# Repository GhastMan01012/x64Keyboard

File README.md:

# x64Keyboard
Source for x64 design

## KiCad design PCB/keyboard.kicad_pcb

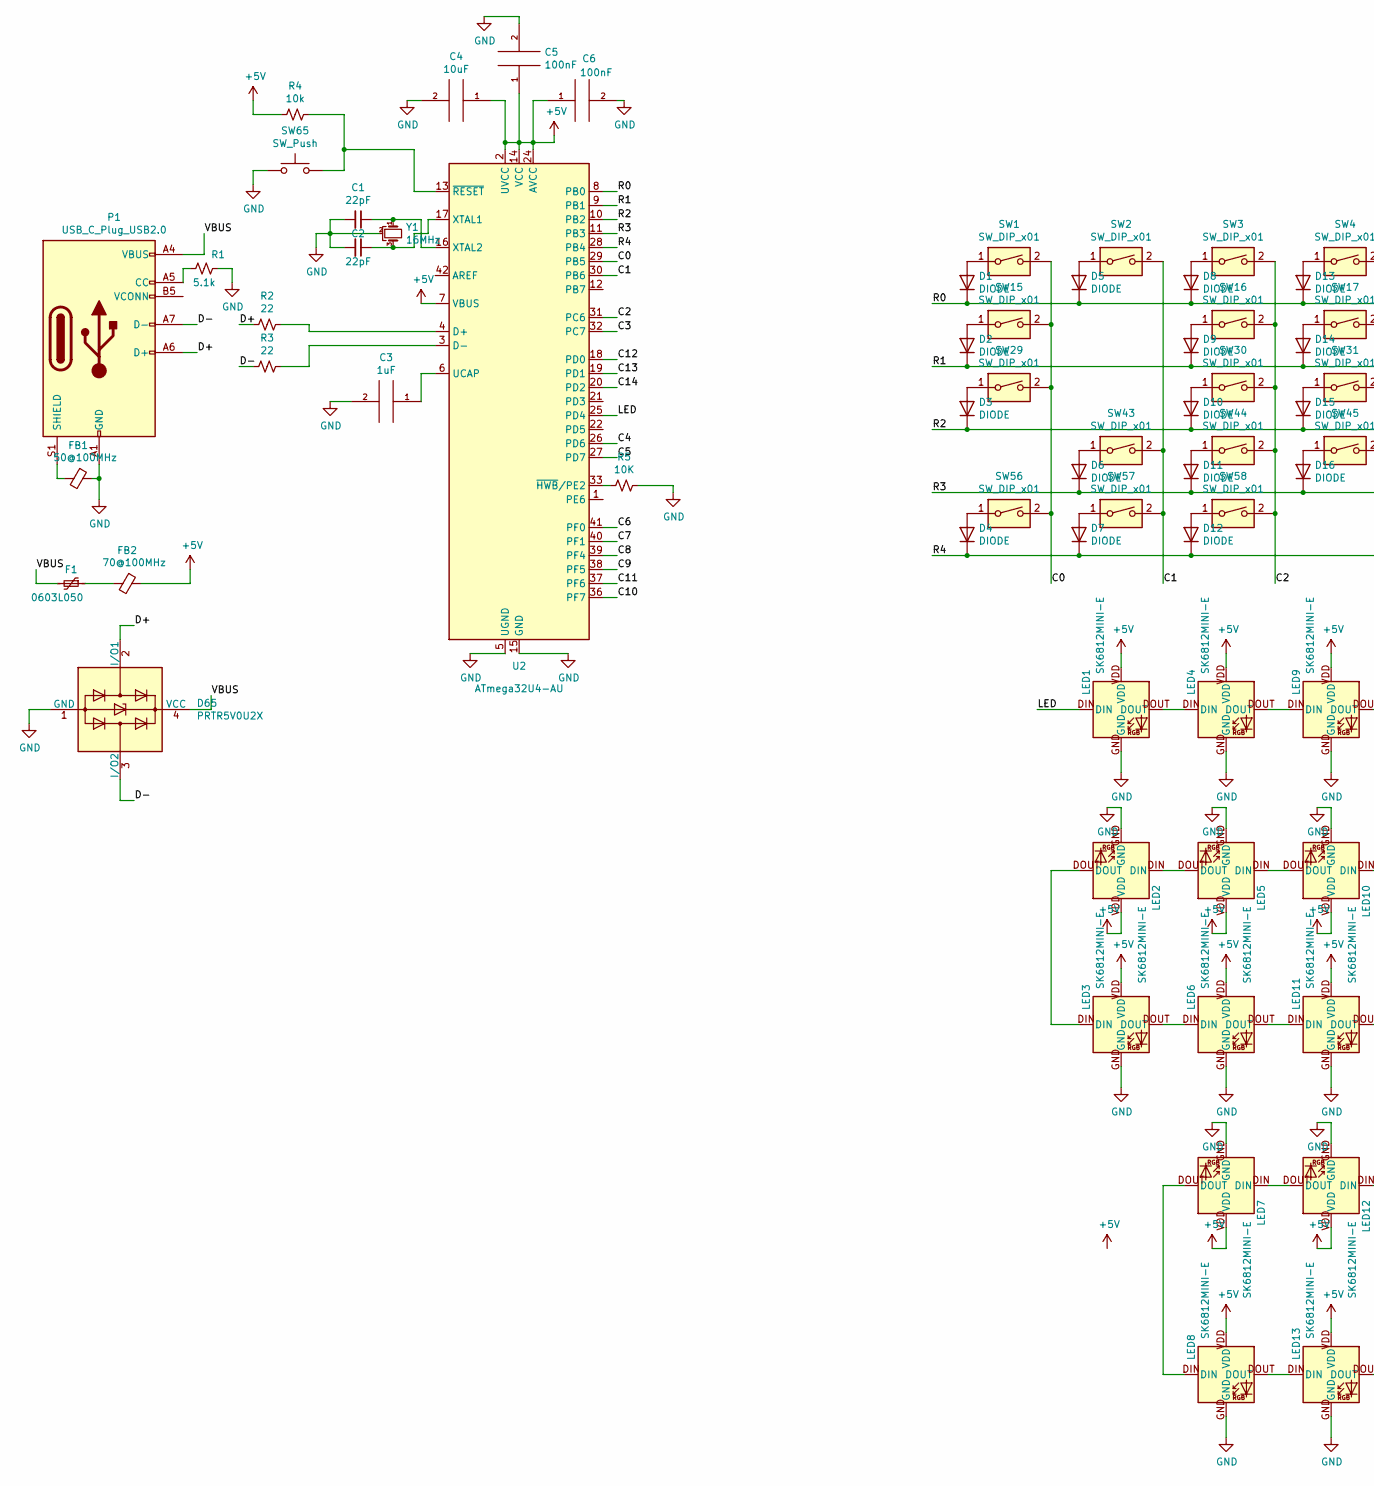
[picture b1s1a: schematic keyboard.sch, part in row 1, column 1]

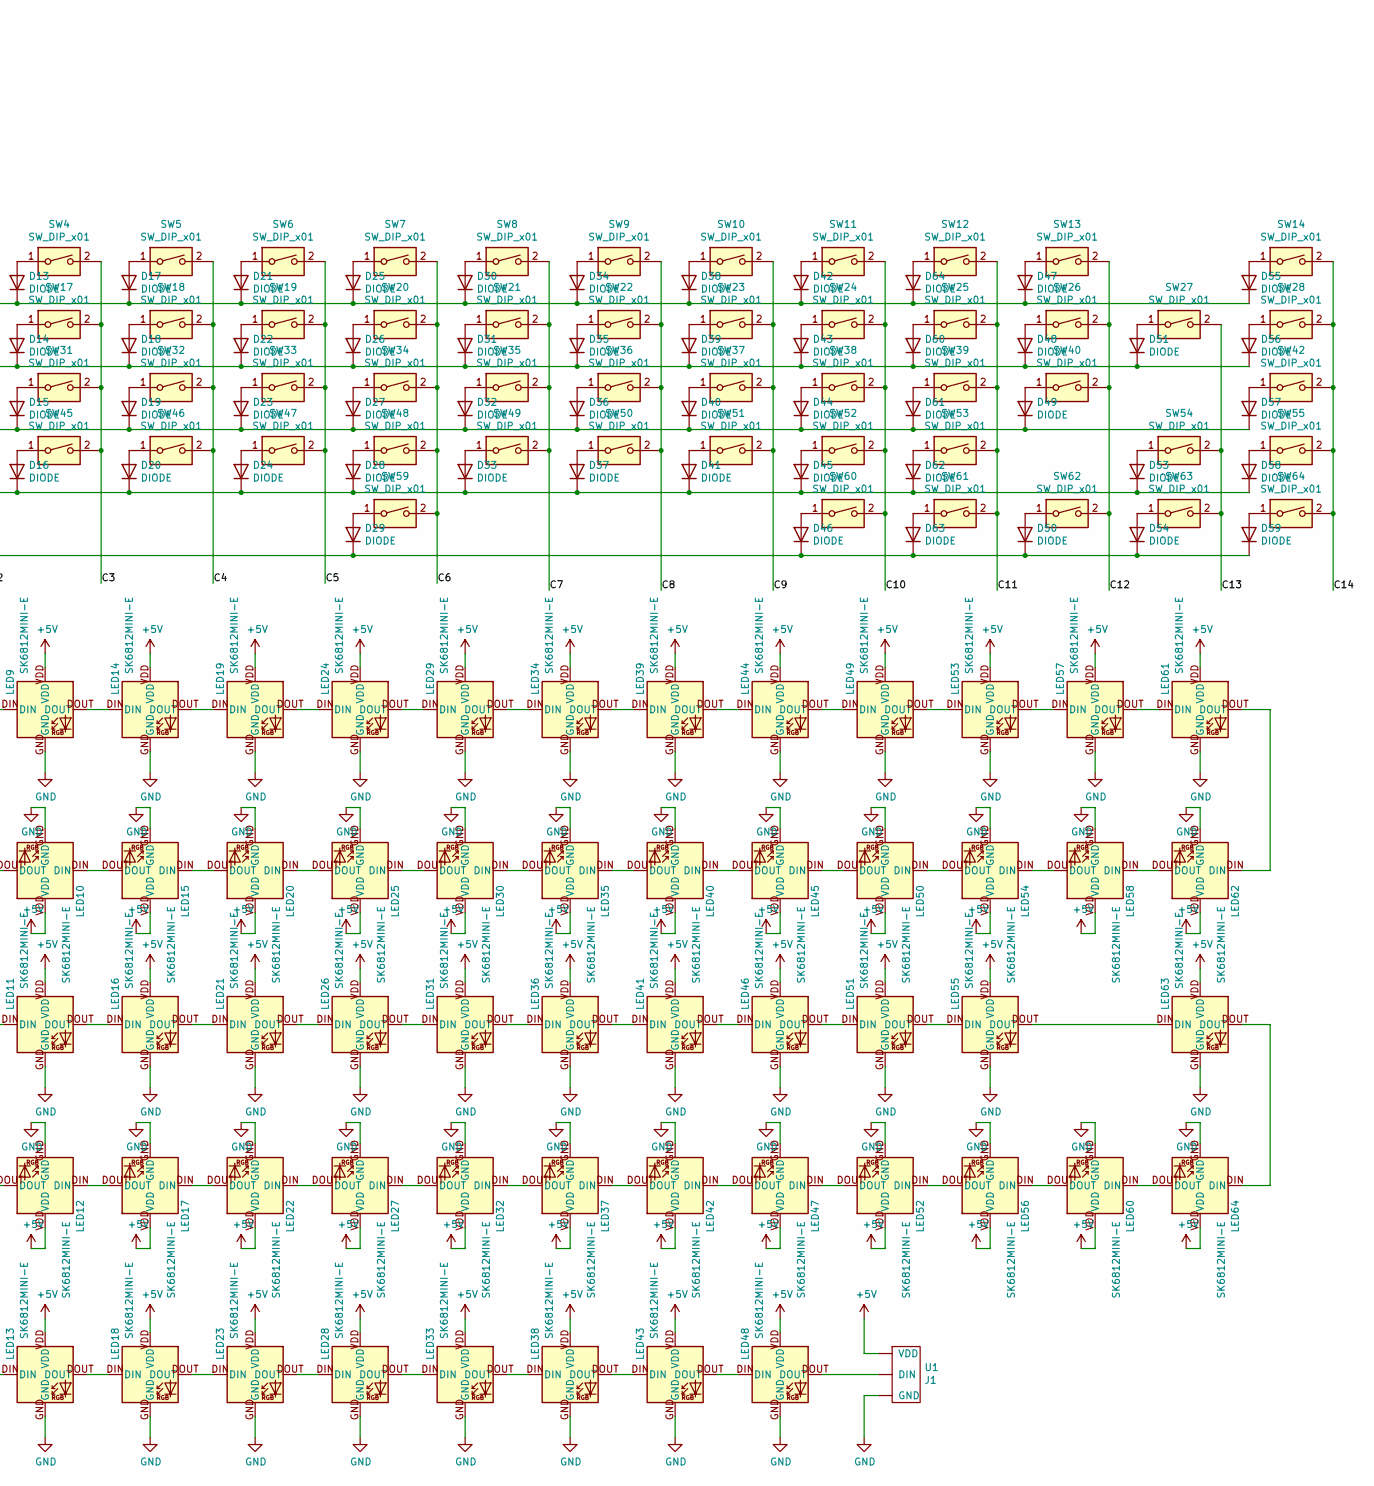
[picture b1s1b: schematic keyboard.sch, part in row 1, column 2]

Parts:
C1, C2: 22pF; C_0603_1608Metric
C3: 1uF; C_0603_1608Metric
C4: 10uF; C_0603_1608Metric
C5, C6: 100nF; C_0603_1608Metric
D1, D2, D3, D4, D5, D6, D7, D8, D9, D10, D11, D12, D13, D14, D15, D16, D17, D18, D19, D20, D21, D22, D23, D24, D25, D26, D27, D28, D29, D30, D31, D32, D33, D34, D35, D36, D37, D38, D39, D40, D41, D42, D43, D44, D45, D46, D47, D48, D49, D50, D51, D53, D54, D55, D56, D57, D58, D59, D60, D61, D62, D63, D64: DIODE; D_SOD-523
D65: PRTR5V0U2X; SOT-143
F1: 0603L050; Fuse_0603_1608Metric
FB1: 50@100MHz; D_0805_2012Metric
FB2: 70@100MHz; D_0805_2012Metric
LED1, LED2, LED3, LED4, LED5, LED6, LED7, LED8, LED9, LED10, LED11, LED12, LED13, LED14, LED15, LED16, LED17, LED18, LED19, LED20, LED21, LED22, LED23, LED24, LED25, LED26, LED27, LED28, LED29, LED30, LED31, LED32, LED33, LED34, LED35, LED36, LED37, LED38, LED39, LED40, LED41, LED42, LED43, LED44, LED45, LED46, LED47, LED48, LED49, LED50, LED51, LED52, LED53, LED54, LED55, LED56, LED57, LED58, LED60, LED61, LED62, LED63, LED64: SK6812MINI-E; LED_SK6812mini-e
P1: USB_C_Plug_USB2.0; USB_C_Receptacle_HRO_TYPE-C-31-M-12
R1: 5.1k; R_0603_1608Metric
R2, R3: 22; R_0603_1608Metric
R4: 10k; R_0603_1608Metric
R5: 10K; R_0603_1608Metric
SW1, SW2, SW3, SW4, SW5, SW6, SW7, SW8, SW9, SW10, SW11, SW12, SW13, SW15, SW16, SW17, SW18, SW19, SW20, SW21, SW22, SW23, SW24, SW25, SW26, SW27, SW28, SW29, SW30, SW31, SW32, SW33, SW34, SW35, SW36, SW37, SW38, SW39, SW40, SW42, SW44, SW45, SW46, SW47, SW48, SW49, SW50, SW51, SW52, SW53, SW54, SW55, SW56, SW57, SW58, SW60, SW61, SW62, SW63, SW64: SW_DIP_x01; SW_Cherry_MX_1.00u_PCB
SW14: SW_DIP_x01; SW_Cherry_MX_2.00u_PCB
SW43: SW_DIP_x01; SW_Cherry_MX_2.25u_PCB
SW59: SW_DIP_x01; SW_Cherry_MX_6.25u_PCB
SW65: SW_Push; SW_Push_1P1T_NO_6x6mm_H9.5mm
U1: J1
U2: ATmega32U4-AU; TQFP-44_10x10mm_P0.8mm
Y1: 16MHz; Crystal_SMD_3225-4Pin_3.2x2.5mm

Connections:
+5V: C4.1, C5.1, C6.1, FB2.1, LED1.VDD, LED2.VDD, LED3.VDD, LED4.VDD, LED5.VDD, LED6.VDD, LED7.VDD, LED8.VDD, LED9.VDD, LED10.VDD, LED11.VDD, LED12.VDD, LED13.VDD, LED14.VDD, LED15.VDD, LED16.VDD, LED17.VDD, LED18.VDD, LED19.VDD, LED20.VDD, LED21.VDD, LED22.VDD, LED23.VDD, LED24.VDD, LED25.VDD, LED26.VDD, LED27.VDD, LED28.VDD, LED29.VDD, LED30.VDD, LED31.VDD, LED32.VDD, LED33.VDD, LED34.VDD, LED35.VDD, LED36.VDD, LED37.VDD, LED38.VDD, LED39.VDD, LED40.VDD, LED41.VDD, LED42.VDD, LED43.VDD, LED44.VDD, LED45.VDD, LED46.VDD, LED47.VDD, LED48.VDD, LED49.VDD, LED50.VDD, LED51.VDD, LED52.VDD, LED53.VDD, LED54.VDD, LED55.VDD, LED56.VDD, LED57.VDD, LED58.VDD, LED60.VDD, LED61.VDD, LED62.VDD, LED63.VDD, LED64.VDD, R4.2, U1.~, U2.2 (UVCC), U2.7 (VBUS), U2.14 (VCC), U2.24 (AVCC), U2.34 (VCC), U2.44 (AVCC)
/C0: SW1.2, SW15.2, SW29.2, SW56.2, U2.29 (PB5)
/C1: SW2.2, SW43.2, SW57.2, U2.30 (PB6)
/C2: SW3.2, SW16.2, SW30.2, SW44.2, SW58.2, U2.31 (PC6)
/C3: SW4.2, SW17.2, SW31.2, SW45.2, U2.32 (PC7)
/C4: SW5.2, SW18.2, SW32.2, SW46.2, U2.26 (PD6)
/C5: SW6.2, SW19.2, SW33.2, SW47.2, U2.27 (PD7)
/C6: SW7.2, SW20.2, SW34.2, SW48.2, SW59.2, U2.41 (PF0)
/C7: SW8.2, SW21.2, SW35.2, SW49.2, U2.40 (PF1)
/C8: SW9.2, SW22.2, SW36.2, SW50.2, U2.39 (PF4)
/C9: SW10.2, SW23.2, SW37.2, SW51.2, U2.38 (PF5)
/C10: SW11.2, SW24.2, SW38.2, SW52.2, SW60.2, U2.36 (PF7)
/C11: SW12.2, SW25.2, SW39.2, SW53.2, SW61.2, U2.37 (PF6)
/C12: SW13.2, SW26.2, SW40.2, SW62.2, U2.18 (PD0)
/C13: SW27.2, SW54.2, SW63.2, U2.19 (PD1)
/C14: SW14.2, SW28.2, SW42.2, SW55.2, SW64.2, U2.20 (PD2)
/D+: D65.2 (I/O1), P1.A6 (D+), R2.2
/D-: D65.3 (I/O2), P1.A7 (D-), R3.2
/LED: LED1.DIN, U2.25 (PD4)
/R0: D1.2 (K), D5.2 (K), D8.2 (K), D13.2 (K), D17.2 (K), D21.2 (K), D25.2 (K), D30.2 (K), D34.2 (K), D38.2 (K), D42.2 (K), D47.2 (K), D55.2 (K), D64.2 (K), U2.8 (PB0)
/R1: D2.2 (K), D9.2 (K), D14.2 (K), D18.2 (K), D22.2 (K), D26.2 (K), D31.2 (K), D35.2 (K), D39.2 (K), D43.2 (K), D48.2 (K), D51.2 (K), D56.2 (K), D60.2 (K), U2.9 (PB1)
/R2: D3.2 (K), D10.2 (K), D15.2 (K), D19.2 (K), D23.2 (K), D27.2 (K), D32.2 (K), D36.2 (K), D40.2 (K), D44.2 (K), D49.2 (K), D57.2 (K), D61.2 (K), U2.10 (PB2)
/R3: D6.2 (K), D11.2 (K), D16.2 (K), D20.2 (K), D24.2 (K), D28.2 (K), D33.2 (K), D37.2 (K), D41.2 (K), D45.2 (K), D53.2 (K), D58.2 (K), D62.2 (K), U2.11 (PB3)
/R4: D4.2 (K), D7.2 (K), D12.2 (K), D29.2 (K), D46.2 (K), D50.2 (K), D54.2 (K), D59.2 (K), D63.2 (K), U2.28 (PB4)
/VBUS: D65.4 (VCC), F1.2, P1.A4 (VBUS), P1.A9 (VBUS), P1.B4 (VBUS), P1.B9 (VBUS)
GND: C1.2, C2.2, C3.2, C4.2, C5.2, C6.2, D65.1 (GND), FB1.1, LED1.GND, LED2.GND, LED3.GND, LED4.GND, LED5.GND, LED6.GND, LED7.GND, LED8.GND, LED9.GND, LED10.GND, LED11.GND, LED12.GND, LED13.GND, LED14.GND, LED15.GND, LED16.GND, LED17.GND, LED18.GND, LED19.GND, LED20.GND, LED21.GND, LED22.GND, LED23.GND, LED24.GND, LED25.GND, LED26.GND, LED27.GND, LED28.GND, LED29.GND, LED30.GND, LED31.GND, LED32.GND, LED33.GND, LED34.GND, LED35.GND, LED36.GND, LED37.GND, LED38.GND, LED39.GND, LED40.GND, LED41.GND, LED42.GND, LED43.GND, LED44.GND, LED45.GND, LED46.GND, LED47.GND, LED48.GND, LED49.GND, LED50.GND, LED51.GND, LED52.GND, LED53.GND, LED54.GND, LED55.GND, LED56.GND, LED57.GND, LED58.GND, LED60.GND, LED61.GND, LED62.GND, LED63.GND, LED64.GND, P1.A1 (GND), P1.A12 (GND), P1.B1 (GND), P1.B12 (GND), R1.2, R5.1, SW65.1, U1.~, U2.5 (UGND), U2.15 (GND), U2.23 (GND), U2.35 (GND), U2.43 (GND), Y1.2
unnamed: C1.1, U2.16 (XTAL2), Y1.1
unnamed: C2.1, U2.17 (XTAL1), Y1.3
unnamed: C3.1, U2.6 (UCAP)
unnamed: D1.1 (A), SW1.1
unnamed: D2.1 (A), SW15.1
unnamed: D3.1 (A), SW29.1
unnamed: D4.1 (A), SW56.1
unnamed: D5.1 (A), SW2.1
unnamed: D6.1 (A), SW43.1
unnamed: D7.1 (A), SW57.1
unnamed: D8.1 (A), SW3.1
unnamed: D9.1 (A), SW16.1
unnamed: D10.1 (A), SW30.1
unnamed: D11.1 (A), SW44.1
unnamed: D12.1 (A), SW58.1
unnamed: D13.1 (A), SW4.1
unnamed: D14.1 (A), SW17.1
unnamed: D15.1 (A), SW31.1
unnamed: D16.1 (A), SW45.1
unnamed: D17.1 (A), SW5.1
unnamed: D18.1 (A), SW18.1
unnamed: D19.1 (A), SW32.1
unnamed: D20.1 (A), SW46.1
unnamed: D21.1 (A), SW6.1
unnamed: D22.1 (A), SW19.1
unnamed: D23.1 (A), SW33.1
unnamed: D24.1 (A), SW47.1
unnamed: D25.1 (A), SW7.1
unnamed: D26.1 (A), SW20.1
unnamed: D27.1 (A), SW34.1
unnamed: D28.1 (A), SW48.1
unnamed: D29.1 (A), SW59.1
unnamed: D30.1 (A), SW8.1
unnamed: D31.1 (A), SW21.1
unnamed: D32.1 (A), SW35.1
unnamed: D33.1 (A), SW49.1
unnamed: D34.1 (A), SW9.1
unnamed: D35.1 (A), SW22.1
unnamed: D36.1 (A), SW36.1
unnamed: D37.1 (A), SW50.1
unnamed: D38.1 (A), SW10.1
unnamed: D39.1 (A), SW23.1
unnamed: D40.1 (A), SW37.1
unnamed: D41.1 (A), SW51.1
unnamed: D42.1 (A), SW11.1
unnamed: D43.1 (A), SW24.1
unnamed: D44.1 (A), SW38.1
unnamed: D45.1 (A), SW52.1
unnamed: D46.1 (A), SW60.1
unnamed: D47.1 (A), SW13.1
unnamed: D48.1 (A), SW26.1
unnamed: D49.1 (A), SW40.1
unnamed: D50.1 (A), SW62.1
unnamed: D51.1 (A), SW27.1
unnamed: D53.1 (A), SW54.1
unnamed: D54.1 (A), SW63.1
unnamed: D55.1 (A), SW14.1
unnamed: D56.1 (A), SW28.1
unnamed: D57.1 (A), SW42.1
unnamed: D58.1 (A), SW55.1
unnamed: D59.1 (A), SW64.1
unnamed: D60.1 (A), SW25.1
unnamed: D61.1 (A), SW39.1
unnamed: D62.1 (A), SW53.1
unnamed: D63.1 (A), SW61.1
unnamed: D64.1 (A), SW12.1
unnamed: F1.1, FB2.2
unnamed: FB1.2, P1.S1 (SHIELD)
unnamed: LED1.DOUT, LED4.DIN
unnamed: LED2.DIN, LED5.DOUT
unnamed: LED2.DOUT, LED3.DIN
unnamed: LED3.DOUT, LED6.DIN
unnamed: LED4.DOUT, LED9.DIN
unnamed: LED7.DOUT, LED8.DIN
unnamed: LED10.DIN, LED15.DOUT
unnamed: LED5.DIN, LED10.DOUT
unnamed: LED6.DOUT, LED11.DIN
unnamed: LED11.DOUT, LED16.DIN
unnamed: LED12.DIN, LED17.DOUT
unnamed: LED7.DIN, LED12.DOUT
unnamed: LED8.DOUT, LED13.DIN
unnamed: LED13.DOUT, LED18.DIN
unnamed: LED9.DOUT, LED14.DIN
unnamed: LED14.DOUT, LED19.DIN
unnamed: LED15.DIN, LED20.DOUT
unnamed: LED16.DOUT, LED21.DIN
unnamed: LED17.DIN, LED22.DOUT
unnamed: LED18.DOUT, LED23.DIN
unnamed: LED19.DOUT, LED24.DIN
unnamed: LED20.DIN, LED25.DOUT
unnamed: LED21.DOUT, LED26.DIN
unnamed: LED22.DIN, LED27.DOUT
unnamed: LED23.DOUT, LED28.DIN
unnamed: LED24.DOUT, LED29.DIN
unnamed: LED25.DIN, LED30.DOUT
unnamed: LED26.DOUT, LED31.DIN
unnamed: LED27.DIN, LED32.DOUT
unnamed: LED28.DOUT, LED33.DIN
unnamed: LED29.DOUT, LED34.DIN
unnamed: LED30.DIN, LED35.DOUT
unnamed: LED31.DOUT, LED36.DIN
unnamed: LED32.DIN, LED37.DOUT
unnamed: LED33.DOUT, LED38.DIN
unnamed: LED34.DOUT, LED39.DIN
unnamed: LED35.DIN, LED40.DOUT
unnamed: LED36.DOUT, LED41.DIN
unnamed: LED37.DIN, LED42.DOUT
unnamed: LED38.DOUT, LED43.DIN
unnamed: LED39.DOUT, LED44.DIN
unnamed: LED40.DIN, LED45.DOUT
unnamed: LED41.DOUT, LED46.DIN
unnamed: LED42.DIN, LED47.DOUT
unnamed: LED43.DOUT, LED48.DIN
unnamed: LED44.DOUT, LED49.DIN
unnamed: LED45.DIN, LED50.DOUT
unnamed: LED46.DOUT, LED51.DIN
unnamed: LED47.DIN, LED52.DOUT
unnamed: LED48.DOUT, U1.~
unnamed: LED49.DOUT, LED53.DIN
unnamed: LED50.DIN, LED54.DOUT
unnamed: LED51.DOUT, LED55.DIN
unnamed: LED52.DIN, LED56.DOUT
unnamed: LED53.DOUT, LED57.DIN
unnamed: LED54.DIN, LED58.DOUT
unnamed: LED55.DOUT, LED63.DIN
unnamed: LED56.DIN, LED60.DOUT
unnamed: LED57.DOUT, LED61.DIN
unnamed: LED58.DIN, LED62.DOUT
unnamed: LED60.DIN, LED64.DOUT
unnamed: LED61.DOUT, LED62.DIN
unnamed: LED63.DOUT, LED64.DIN
unnamed: P1.A5 (CC), R1.1
unnamed: R2.1, U2.4 (D+)
unnamed: R3.1, U2.3 (D-)
unnamed: R4.1, SW65.2, U2.13 (~RESET)
unnamed: R5.2, U2.33 (~HWB~/PE2)

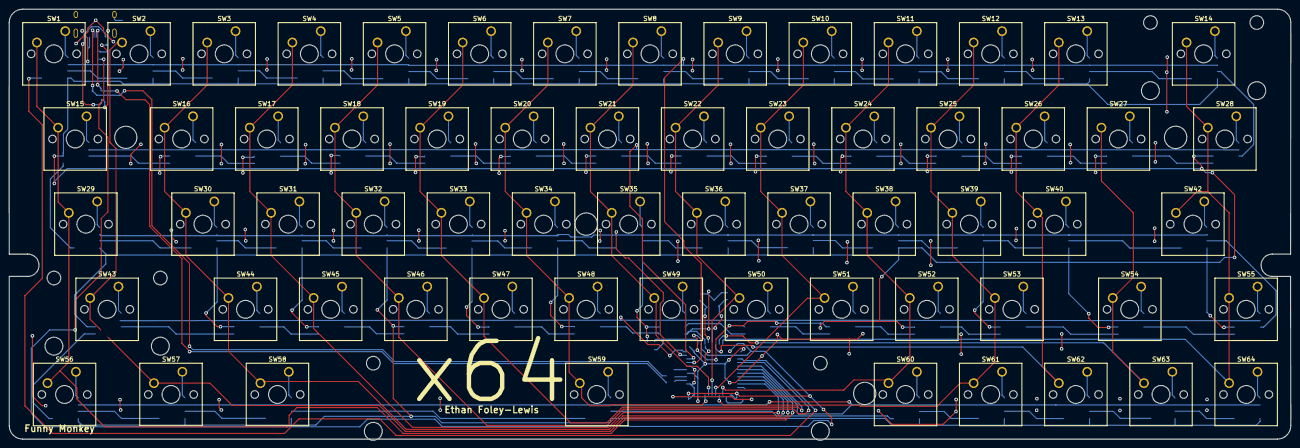
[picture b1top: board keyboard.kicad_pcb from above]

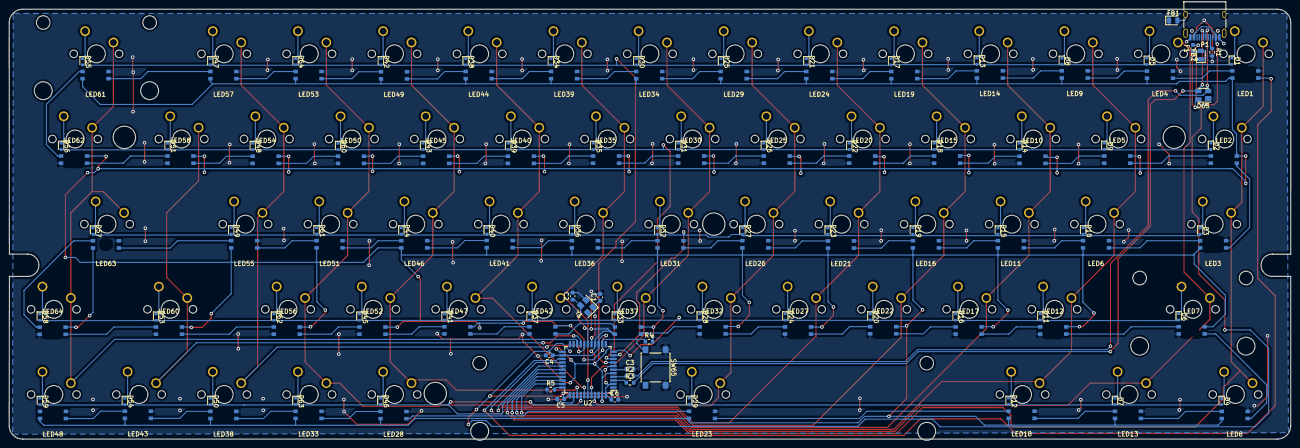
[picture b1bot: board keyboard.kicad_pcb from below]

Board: 2 copper layers, 286.7 x 96.2 mm, 208 parts (145 on the bottom side), 161 nets.

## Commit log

2021-03-30 PCB Upload
    Just PCB schematic and design
